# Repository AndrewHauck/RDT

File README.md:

# Missouri S&T Rocket Design
This is the official repository of the Missouri Rocket Design Team. The purpose of this repository is to allow collaboration on PCB development and software development

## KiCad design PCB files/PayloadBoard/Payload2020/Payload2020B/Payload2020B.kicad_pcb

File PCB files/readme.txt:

The home of all RDT board design projects

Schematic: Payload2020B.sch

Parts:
H1, H2, H3, H4: Corner; MountingHole_4-40
J1: BridgeConn; JST_SH_SM15B-SRSS-TB_1x15-1MP_P1.00mm_Horizontal
U1: Xbee_XBP9B; XBEE-1
U2: BerryIMUv3; BerryGPS-IMU_V3

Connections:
+3.3VA: J1.5, U1.1 (VCC)
+3V3: J1.10, U2.1
/Berry_SCL: J1.2, U2.3
/Berry_SDA: J1.1, U2.2
/RX_GPS: J1.3, U2.7
/TX_GPS: J1.4, U2.8
/XBEE_CTS: J1.7, U1.12 (~CTS)
/XBEE_DIN: J1.9, U1.3 (DIN)
/XBEE_DOUT: J1.8, U1.2 (DOUT)
/XBEE_RTS: J1.6, U1.16 (~RTS)
GNDREF: U1.10 (GND), U2.6
unnamed: J1.11, U2.9
unnamed: J1.12, U2.10
unnamed: J1.13, U2.11
unnamed: J1.14, U2.12
unnamed: J1.15, U2.13

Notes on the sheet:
2020 Payload Board B
Project created Feb 16 2020
10mil grid
Xbee Serial pins DOUT DIN CTS RTS

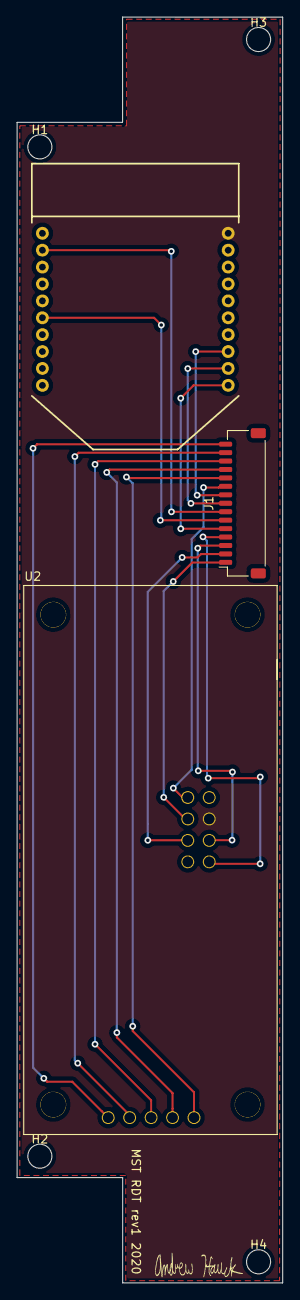
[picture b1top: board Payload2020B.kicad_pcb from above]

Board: 2 copper layers, 31.4 x 149.9 mm, 7 parts (0 on the bottom side), 16 nets.

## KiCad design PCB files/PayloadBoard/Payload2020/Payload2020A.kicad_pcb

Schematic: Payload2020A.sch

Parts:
C1, C2: 1uF; C_1206_3216Metric
C3, C4: 10uF; C_1206_3216Metric
D1, D2: LED; LED_1206_3216Metric
H1, H2, H3, H4: Corner; MountingHole_4-40
J1: BATTERY; JST_XH_B2B-XH-AM_1x02_P2.50mm_Vertical
J2: BridgeConn; JST_SH_SM15B-SRSS-TB_1x15-1MP_P1.00mm_Horizontal
J3: LoadCell; Molex_PicoBlade_53047-0410_1x04_P1.25mm_Vertical
L1: 2.2uH; L_1210_3225Metric
Q1, Q2: Q_NMOS_GSD; SOT-23
R1: 1k; R_0805_2012Metric_Pad1.15x1.40mm_HandSolder
R2: 100k; R_0805_2012Metric_Pad1.15x1.40mm_HandSolder
R3, R6: 100; R_0805_2012Metric_Pad1.15x1.40mm_HandSolder
R4, R5: 10k; R_0805_2012Metric_Pad1.15x1.40mm_HandSolder
SW1: SW_SPST; GW12RCH
U1: Teensy3.6; Teensy35_36
U2: ArduCam
U3: HX711_Breakout
U4: AP7370-50W5-7; SOT-23-5
U5: TPS613222ADBVR; SOT-23-5

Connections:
+3.3VA: C2.1, J2.5, U4.5
+3V3: J2.10, U1.26 (3V3), U2.6 (VCC), U3.10 (VCC)
+5V: C3.1, C4.1, D1.2, D2.2, R1.1, R4.1, U1.53 (VIN), U5.4
/Ardu_CS: U1.11 (9_PWM_RX2_CS0), U2.1 (CS)
/Ardu_MISO: U1.14 (12_MISO0), U2.3 (MISO)
/Ardu_MOSI: U1.13 (11_MOSI0), U2.2 (MOSI)
/Ardu_SCK: U1.40 (13_SCK0_LED), U2.4 (SCK)
/Ardu_SCL: U1.45 (18_A4_SDA0_TOUCH)
/Ardu_SDA: U1.46 (19_A5_SCL0_TOUCH)
/Berry_SCL: J2.2, U1.5 (3_PWM_CAN0TX_SCL2)
/Berry_SDA: J2.1, U1.6 (4_PWM_CAN0RX_SDA2)
/DEN_G: J2.11, U1.7 (5_PWM_TX1_MISO1)
/DRDY_G: J2.13, U1.10 (8_TX3_MISO0_SDA0)
/HX_CLK: U1.3 (1_TX1_MISO1_TOUCH), U3.9 (SCK)
/HX_OUT: U1.2 (0_RX1_MOSI1_TOUCH), U3.8 (DOUT)
/INT1_XM: J2.14, U1.12 (10_PWM_TX2_CS0)
/INT2_XM: J2.15, U1.15 (3.3V)
/INT_G: J2.12, U1.9 (7_RX3_MISO0_SCL0)
/RX_GPS: J2.3, U1.19 (27_RX1)
/TX_GPS: J2.4, U1.18 (26_TX1)
/USR_LED1: Q1.1, R1.2, R2.1, U1.4 (2_PWM)
/USR_LED2: Q2.1, R4.2, R5.1, U1.8 (6_PWM)
/XBEE_CTS: J2.7, U1.17 (25)
/XBEE_DIN: J2.9, U1.21 (29_PWM_CAN0TX_TOUCH)
/XBEE_DOUT: J2.8, U1.20 (28)
/XBEE_RTS: J2.6, U1.16 (24)
GNDREF: C1.1, C2.2, C3.2, C4.2, J1.2, R2.2, R3.2, R5.2, R6.2, U1.1 (GND), U1.27 (GND), U1.39 (GND), U1.52 (AGND), U1.~ (3.3V), U2.5 (GND), U3.7 (GND), U4.2, U5.2
unnamed: C1.2, L1.1, SW1.2, U4.1
unnamed: D1.1, Q1.3
unnamed: D2.1, Q2.3
unnamed: J1.1, SW1.1
unnamed: J3.1, U3.1 (E+)
unnamed: J3.2, U3.2 (E-)
unnamed: J3.3, U3.3 (A-)
unnamed: J3.4, U3.4 (A+)
unnamed: L1.2, U5.1
unnamed: Q1.2, R3.1
unnamed: Q2.2, R6.1
unnamed: U1.34 (37_A18_PWM_SCL1), U2.8 (SCL)
unnamed: U1.35 (38_A19_PWM_SDA1), U2.7 (SDA)

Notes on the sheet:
2020 Payload board A
Project created 2/15/2020
Load Cell ADC
3-4.2V
1sXp LiON
3V3A - Power to Xbee from battery 3V3 - Power to ArduCam, HX711, and BerryIMU from Teensy
<--- from boost converter
Voltage Boost/Regulation
USER CONTROLLED LEDS

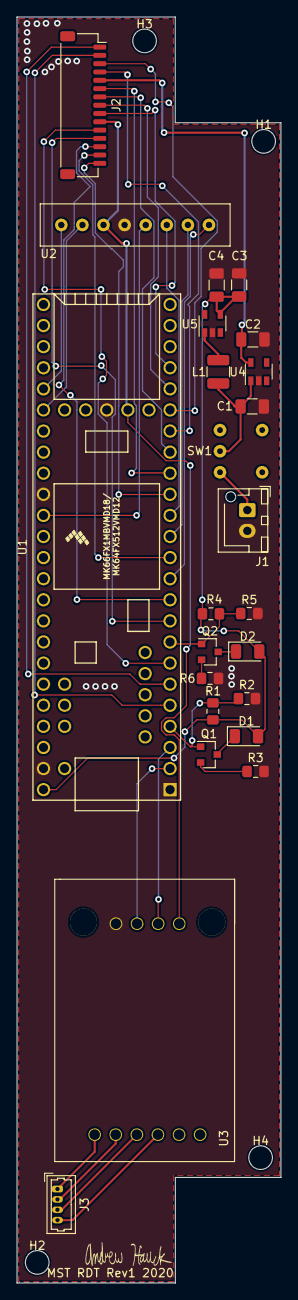
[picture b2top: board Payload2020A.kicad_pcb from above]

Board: 2 copper layers, 31.8 x 152.4 mm, 28 parts (0 on the bottom side), 38 nets.

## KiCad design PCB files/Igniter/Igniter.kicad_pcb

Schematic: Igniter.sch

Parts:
D1: D_Small; D_SOD-123F
D2, D3, D4, D5, D6: D; D_SOD-123F
D7, D8, D9, D10, D11: LED; LED_1206_3216Metric
D12: 3V3; LED_1206_3216Metric
D13: 24V; LED_1206_3216Metric
D14: ACT; LED_1206_3216Metric
F1: BladeFuse; FuseHolder
IC1: 74HC4050; SOP-16_4.4x10.4mm_P1.27mm
J1, J2, J3, J4: PT; Molex_SPOX_5267-03A_1x03_P2.50mm_Vertical
J5: Battery; Molex_Mini-Fit_Jr_5566-02A_2x01_P4.20mm_Vertical
J6, J7: COIL; BananaJack15.5mm
J8, J9, J10, J11, J12: SL1; Molex_SPOX_5267-03A_1x03_P2.50mm_Vertical
J13: Micro_SD_Card; microSD_HC_Hirose_DM3BT-DSF-PEJS
MH1, MH2, MH3, MH4: MountingHole; MountingHole_3.5mm
Q1: IGN; SOT-223
Q2, Q3, Q4, Q5, Q6: Q_NMOS_GDSD; SOT-223
R1: 200; R_1206_3216Metric
R2, R3, R6, R11, R12, R15: 10k; R_1206_3216Metric
R4, R5, R7, R8, R9, R10: 1k2; R_1206_3216Metric
R13: 1k; R_1206_3216Metric
SW1: ARM; R1966ABLKBLKFR-SPST
U1: Teensy3.2; Teensy30_31_32_LC
U2, U3, U4: FDS8984; SO-8_5.3x6.2mm_P1.27mm

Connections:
+3V3: IC1.1 (VCC), J13.4 (VDD), R1.2, U1.15, U1.26, U1.51
+24V: D1.1 (K), D2.1 (K), D3.1 (K), D4.1 (K), D5.1 (K), D6.1 (K), F1.1 (A), F1.2 (A), F1.3 (A), F1.4 (A), J1.3, J2.3, J3.3, J4.3, J6.1, J6.2, J8.3, J9.3, J10.3, J11.3, J12.3, R4.2, U2.5 (Drain2), U2.6 (Drain2), U2.7 (Drain1), U2.8 (Drain1), U3.5 (Drain2), U3.6 (Drain2), U3.7 (Drain1), U3.8 (Drain1), U4.7 (Drain1), U4.8 (Drain1)
/PT0: J1.2, U1.44
/PT1: J2.2, U1.43
/PT2: J3.2, U1.42
/PT3: J4.2, U1.41
/SOL1: Q2.1 (G), R15.1, U1.5, U2.2 (Gate1)
/SOL2: Q3.1 (G), R2.1, U1.6, U2.4 (Gate2)
/SOL3: Q4.1 (G), R3.1, U1.7, U3.2 (Gate1)
/SOL4: Q5.1 (G), R11.1, U1.8, U3.4 (Gate2)
/SOL5: Q6.1 (G), R12.1, U1.9, U4.2 (Gate1)
/SPRK: Q1.1 (G), R6.2, U1.4
GNDREF: D7.1 (K), D8.1 (K), D9.1 (K), D10.1 (K), D11.1 (K), D12.1 (K), D13.1 (K), IC1.8 (GND), IC1.14 (6A), J1.1, J2.1, J3.1, J4.1, J5.2, J8.1, J9.1, J10.1, J11.1, J12.1, J13.6 (VSS), Q1.3 (S), Q2.3 (S), Q3.3 (S), Q4.3 (S), Q5.3 (S), Q6.3 (S), R2.2, R3.2, R6.1, R11.2, R12.2, R15.2, U1.1, U1.27, U1.39, U1.52
unnamed: D1.2 (A), J7.1, J7.2, Q1.2 (D), Q1.4 (D)
unnamed: D2.2 (A), J8.2, Q2.2 (D), Q2.4 (D)
unnamed: D3.2 (A), J9.2, Q3.2 (D), Q3.4 (D)
unnamed: D4.2 (A), J10.2, Q4.2 (D), Q4.4 (D)
unnamed: D5.2 (A), J11.2, Q5.2 (D), Q5.4 (D)
unnamed: D6.2 (A), J12.2, Q6.2 (D), Q6.4 (D)
unnamed: D7.2 (A), R5.1
unnamed: D8.2 (A), R8.2
unnamed: D9.2 (A), R7.1
unnamed: D10.2 (A), R9.2
unnamed: D11.2 (A), R10.2
unnamed: D12.2 (A), R1.1
unnamed: D13.2 (A), R4.1
unnamed: D14.1 (K), R13.2
unnamed: D14.2 (A), IC1.10 (4Y), J13.7 (DAT0)
unnamed: F1.5 (B), F1.6 (B), F1.7 (B), F1.8 (B), SW1.1 (A)
unnamed: IC1.2 (1Y), J13.5 (CLK)
unnamed: IC1.4 (2Y), J13.3 (CMD)
unnamed: IC1.6 (3Y), J13.2 (DAT3/CD), R13.1
unnamed: J5.1, SW1.2 (B)
unnamed: R5.2, U2.3 (Source2)
unnamed: R7.2, U3.3 (Source2)
unnamed: R8.1, U2.1 (Source1)
unnamed: R9.1, U3.1 (Source1)
unnamed: R10.1, U4.1 (Source1)

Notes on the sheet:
24V battery connection
Status Indicators
Board Standoffs
Pressure Transducers
Vcc 200mA max current draw for ATmega2560 -SD card powered by atmega 3V3 pin
-Board sits at test operator area
NOTES
Igniter Arduino Shield
10 mil grid
Solenoid indicators
Igniter Driver
Solenoid Drivers

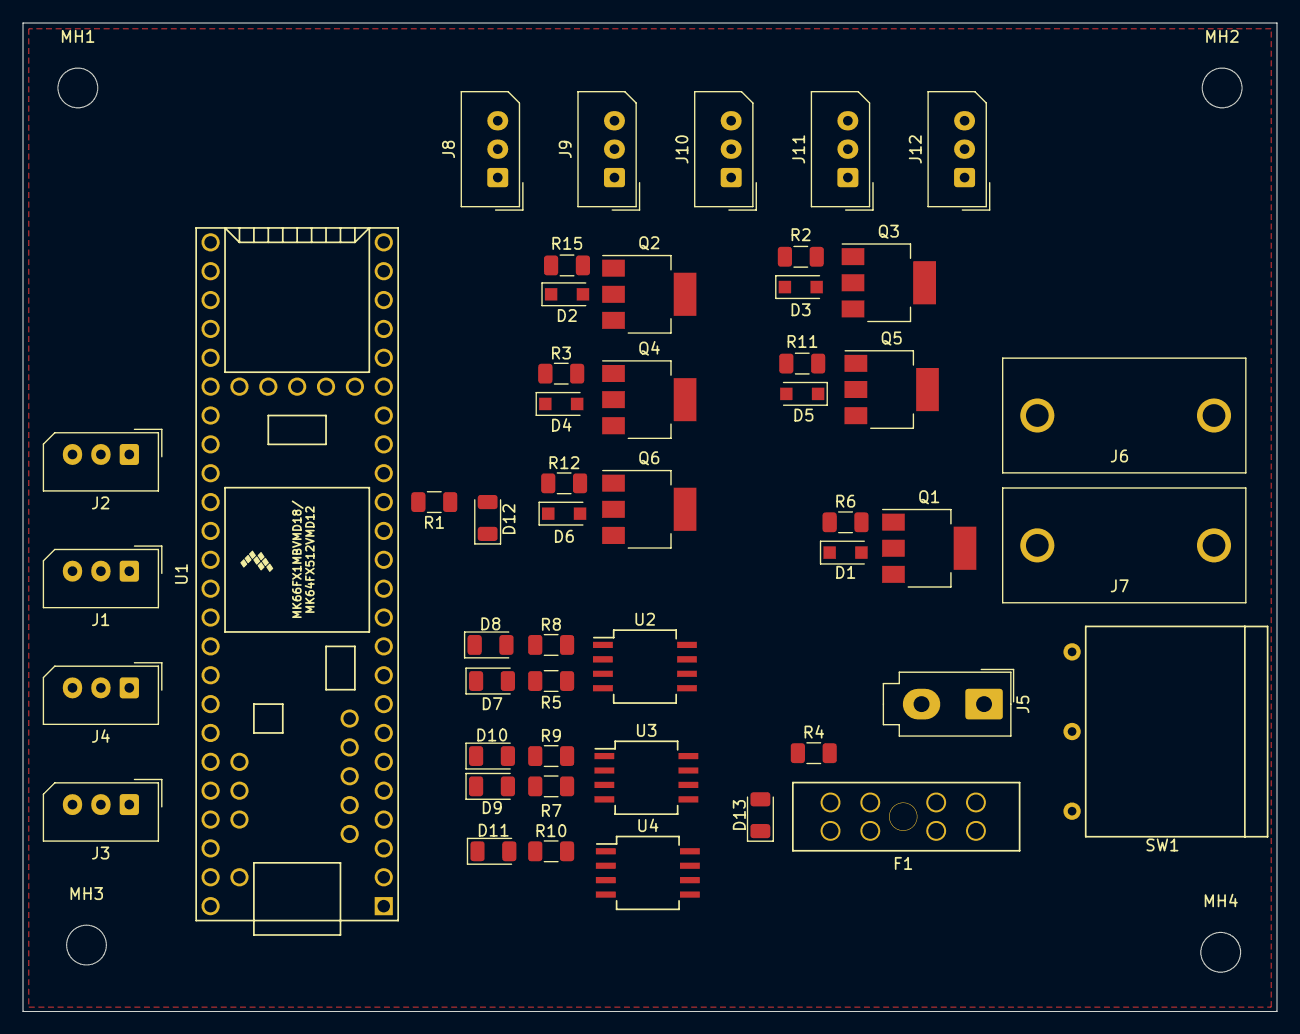
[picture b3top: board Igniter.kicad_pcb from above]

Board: 2 copper layers, 110.4 x 87.0 mm, 54 parts (0 on the bottom side), 33 nets, no tracks yet.

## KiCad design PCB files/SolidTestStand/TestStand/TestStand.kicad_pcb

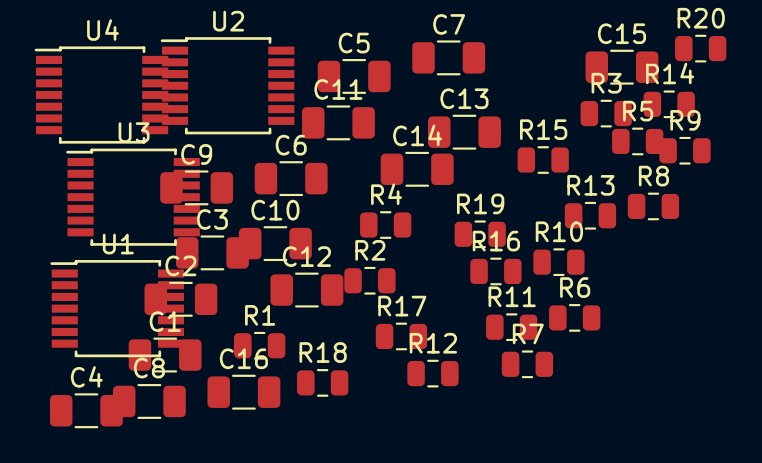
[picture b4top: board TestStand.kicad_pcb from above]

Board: 2 copper layers, 40 parts (0 on the bottom side), 17 nets, no tracks yet.

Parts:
C1, C3, C4, C6, C9, C11, C12, C14: 0.01u; C_1206_3216Metric
C2, C5, C7, C8, C10, C13, C15, C16: 0.1u; C_1206_3216Metric
R1, R2, R3, R4, R11, R12, R13, R14: 100; R_0805_2012Metric
R5, R6, R7, R8, R9, R10, R15, R16, R17, R18, R19, R20: 10k; R_0805_2012Metric
U1, U2, U3, U4: MAX31856; TSSOP-14_4.4x5mm_P0.65mm

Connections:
+3V3: C7.2, C8.2, C15.2, C16.2, R5.2, R6.2, R7.2, R8.2, R9.2, R10.2, R15.2, R16.2, R17.2, R18.2, R19.2, R20.2, U1.5, U1.8, U2.5, U2.8, U3.5, U3.8, U4.5, U4.8
/BIAS: R1.2, R3.2, R11.2, R13.2, U1.2, U2.2, U3.2, U4.2
/SCK: R7.1, R8.1, R17.1, R18.1, U1.10, U2.10, U3.10, U4.10
/SDI: R5.1, R6.1, R15.1, R16.1, U1.12, U2.12, U3.12, U4.12
/SDO: U1.11, U2.11, U3.11, U4.11
/~CS: R9.1, R10.1, R19.1, R20.1, U1.9, U2.9, U3.9, U4.9
/~DRDY: U1.7, U2.7, U3.7, U4.7
/~FAULT: U1.13, U2.13, U3.13, U4.13
GNDREF: C1.1, C3.2, C4.1, C6.2, C7.1, C8.1, C9.1, C11.2, C12.1, C14.2, C15.1, C16.1, U1.1, U1.14, U2.1, U2.14, U3.1, U3.14, U4.1, U4.14
unnamed: C1.2, C2.1, R1.1, U1.3
unnamed: C2.2, C3.1, R2.1, U1.4
unnamed: C4.2, C5.1, R3.1, U2.3
unnamed: C5.2, C6.1, R4.1, U2.4
unnamed: C9.2, C10.1, R11.1, U3.3
unnamed: C10.2, C11.1, R12.1, U3.4
unnamed: C12.2, C13.1, R13.1, U4.3
unnamed: C13.2, C14.1, R14.1, U4.4

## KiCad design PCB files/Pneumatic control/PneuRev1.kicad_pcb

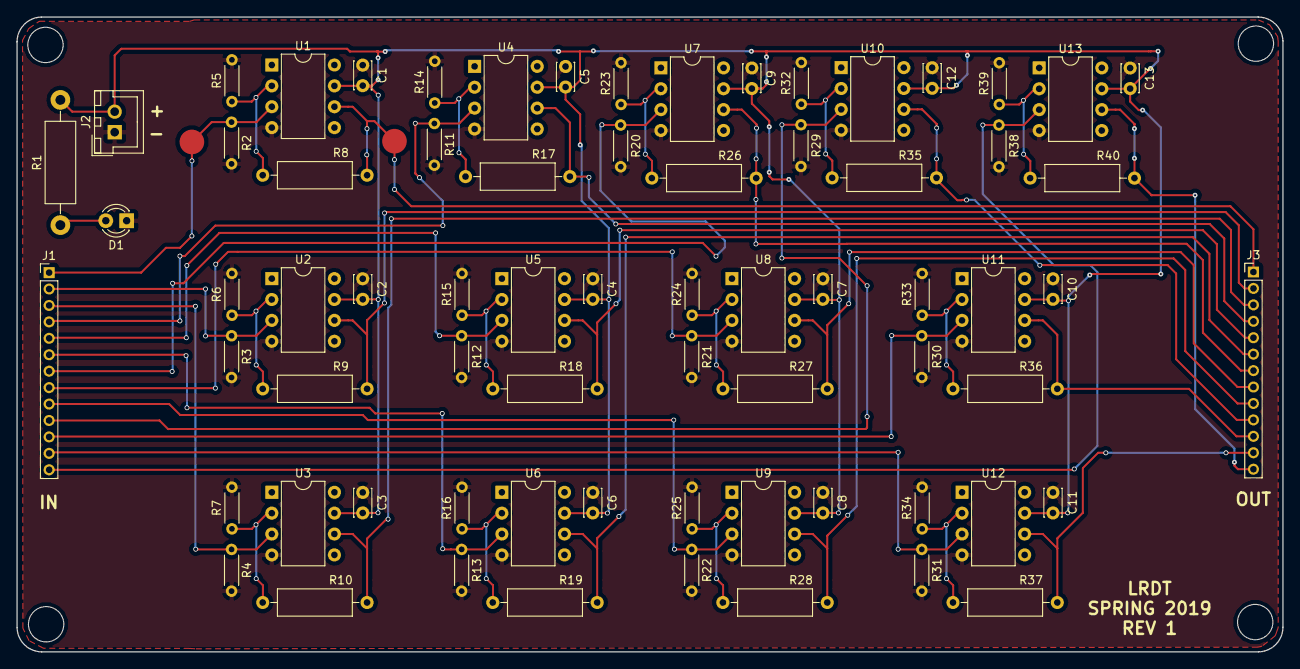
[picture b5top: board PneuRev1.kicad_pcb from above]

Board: 2 copper layers, 154.1 x 77.3 mm, 72 parts (0 on the bottom side), 42 nets.

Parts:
C1, C2, C3, C4, C5, C6, C7, C8, C9, C10, C11, C12, C13: 1uF; C_Disc_D3.4mm_W2.1mm_P2.50mm
D1: LED; LED_D3.0mm
J1: SIG_IN; Pin_Header_Straight_1x13_Pitch2.00mm
J2: BATT_IN; JST_XH_B02B-XH-A_02x2.50mm_Straight
J3: PNEU; Pin_Header_Straight_1x13_Pitch2.00mm
R1: 3k; R_Axial_DIN0411_L9.9mm_D3.6mm_P15.24mm_Horizontal
R2, R3, R4, R5, R6, R7, R11, R12, R13, R14, R15, R16, R20, R21, R22, R23, R24, R25, R29, R30, R31, R32, R33, R34, R38, R39: 1k; R_Axial_DIN0204_L3.6mm_D1.6mm_P5.08mm_Horizontal
R8, R9, R10, R17, R18, R19, R26, R27, R28, R35, R36, R37, R40: 4k; R_Axial_DIN0309_L9.0mm_D3.2mm_P12.70mm_Horizontal
TP1, TP2: TEST; Measurement_Point_Round-SMD-Pad_Big
U1, U2, U3, U4, U5, U6, U7, U8, U9, U10, U11, U12, U13: OPA551; DIP-8_W7.62mm

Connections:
/IN2: J1.2, R3.1, U2.3
/IN3: J1.3, R4.1, U3.3
/IN4: J1.4, R11.1, U4.3
/IN5: J1.5, R12.1, U5.3
/IN6: J1.6, R13.1, U6.3
/IN7: J1.7, R20.1, U7.3
/IN8: J1.8, R21.1, U8.3
/IN9: J1.9, R22.1, U9.3
/IN10: J1.10, R29.1, U10.3
/IN11: J1.11, R30.1, U11.3
/IN12: J1.12, R31.1, U12.3
/IN13: J1.13, R38.1, U13.3
/PNU1: J3.1, R8.2, TP2.1, U1.6
/PNU2: J3.2, R9.2, U2.6
/PNU3: J3.3, R10.2, U3.6
/PNU4: J3.4, R17.2, U4.6
/PNU5: J3.5, R18.2, U5.6
/PNU6: J3.6, R19.2, U6.6
/PNU7: J3.7, R26.2, U7.6
/PNU8: J3.8, R27.2, U8.6
/PNU9: J3.9, R28.2, U9.6
/PNU10: J3.10, R35.2, U10.6
/PNU11: J3.11, R36.2, U11.6
/PNU12: J3.12, R37.2, U12.6
/PNU13: J3.13, R40.2, U13.6
GND: C1.1, C2.1, C3.1, C4.1, C5.1, C6.1, C7.1, C8.1, C9.1, C10.1, C11.1, C12.1, C13.1, D1.1, J2.1, R2.2, R3.2, R4.2, R5.2, R6.2, R7.2, R11.2, R12.2, R13.2, R14.2, R15.2, R16.2, R20.2, R21.2, R22.2, R23.2, R24.2, R25.2, R29.2, R30.2, R31.2, R32.2, R33.2, R34.2, R38.2, R39.2, U1.4, U2.4, U3.4, U4.4, U5.4, U6.4, U7.4, U8.4, U9.4, U10.4, U11.4, U12.4, U13.4
unnamed: C1.2, C2.2, C3.2, C4.2, C5.2, C6.2, C7.2, C8.2, C9.2, C10.2, C11.2, C12.2, C13.2, J2.2, R1.2, U1.7, U2.7, U3.7, U4.7, U5.7, U6.7, U7.7, U8.7, U9.7, U10.7, U11.7, U12.7, U13.7
unnamed: D1.2, R1.1
unnamed: J1.1, R2.1, TP1.1, U1.3
unnamed: R5.1, R8.1, U1.2
unnamed: R6.1, R9.1, U2.2
unnamed: R7.1, R10.1, U3.2
unnamed: R14.1, R17.1, U4.2
unnamed: R15.1, R18.1, U5.2
unnamed: R16.1, R19.1, U6.2
unnamed: R23.1, R26.1, U7.2
unnamed: R24.1, R27.1, U8.2
unnamed: R25.1, R28.1, U9.2
unnamed: R32.1, R35.1, U10.2
unnamed: R33.1, R36.1, U11.2
unnamed: R34.1, R37.1, U12.2
unnamed: R39.1, R40.1, U13.2

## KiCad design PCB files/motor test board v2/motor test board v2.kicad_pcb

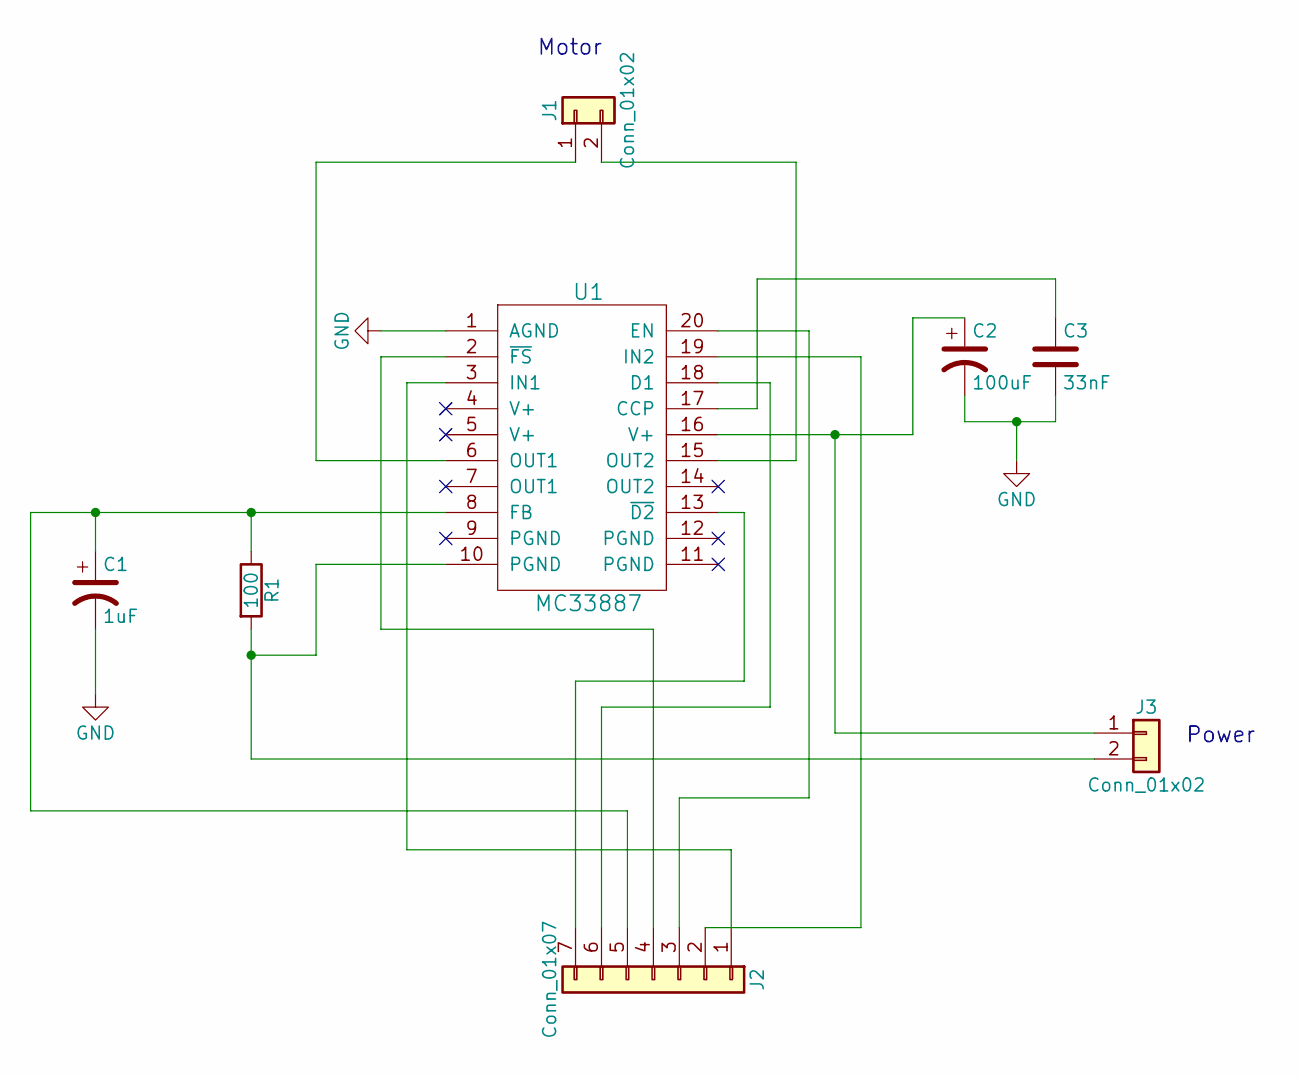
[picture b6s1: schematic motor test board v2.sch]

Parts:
C1: 1uF; CP_Tantalum_Case-C_EIA-6032-28_Hand
C2: 100uF; CP_Elec_8x6.5
C3: 33nF; C_1812_HandSoldering
J1, J3: Conn_01x02; TerminalBlock_Altech_AK300-2_P5.00mm
J2: Conn_01x07; Pin_Header_Straight_1x07_Pitch2.00mm
R1: 100; R_2512_HandSoldering
U1: MC33887; SOIC127P1420X340-21N

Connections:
GND: C1.2, C2.2, C3.2, U1.1 (AGND)
unnamed: C1.1, J2.5, R1.1, U1.8 (FB)
unnamed: C2.1, J3.1, U1.16 (V+)
unnamed: C3.1, U1.17 (CCP)
unnamed: J1.1, U1.6 (OUT1)
unnamed: J1.2, U1.15 (OUT2)
unnamed: J2.1, U1.3 (IN1)
unnamed: J2.2, U1.19 (IN2)
unnamed: J2.3, U1.20 (EN)
unnamed: J2.4, U1.2 (~FS)
unnamed: J2.6, U1.18 (D1)
unnamed: J2.7, U1.13 (~D2)
unnamed: J3.2, R1.2, U1.10 (PGND)

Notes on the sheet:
Motor
Power

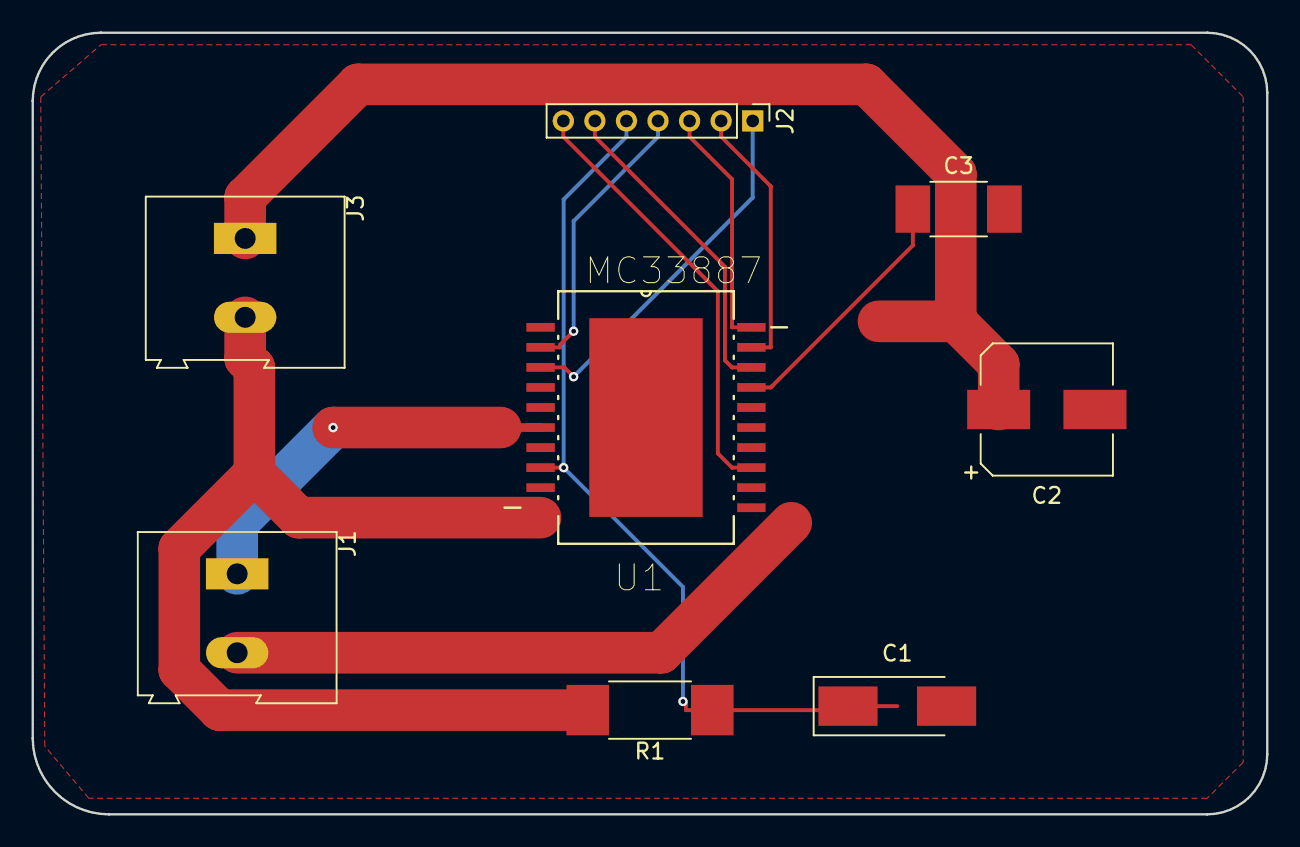
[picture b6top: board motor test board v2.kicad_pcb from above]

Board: 2 copper layers, 78.2 x 49.5 mm, 8 parts (0 on the bottom side), 13 nets.

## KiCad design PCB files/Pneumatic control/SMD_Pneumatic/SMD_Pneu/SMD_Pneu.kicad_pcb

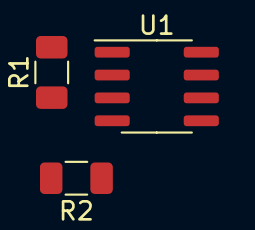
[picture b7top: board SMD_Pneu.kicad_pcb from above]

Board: 2 copper layers, 3 parts (0 on the bottom side), 2 nets, no tracks yet.

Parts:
R1, R2: R; R_1206_3216Metric
U1: LM321; SOIC-8_3.9x4.9mm_P1.27mm

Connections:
unnamed: R1.1, R2.2, U1.3
unnamed: R2.1, U1.4

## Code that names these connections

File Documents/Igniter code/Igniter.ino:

/*
OFFICIAL ROCKET IGNITER CODE
This .ino file is the main program to be run on the 2560 board

 * SD card attached to SPI bus as follows on MEGA2560:
 ** MOSI = DI - pin 51
 ** MISO = DO - pin 50
 ** CLK - pin 52
 ** CS - pin 53

 */
#include <SPI.h>
#include <SD.h>

File myFile;

//Define pressure transducer analog pin variables
int PT1 = A0;
int PT2 = A1;
int PT3 = A2;
int PT4 = A3;

//Define variables for raw data read on analog pins
int pdata1;
int pdata2;
int pdata3;
int pdata4;

//Define pressure pin voltage variables
float V1 = A0;
float V2 = A1;
float V3 = A2;
float V4 = A3;

//Define pressure variables
float P1;
float P2;
float P3;
float P4;

//Time in msec for delay function
int sleep=200;

//Define SPI pins for SD card interface
int CS = 53;
int MOSI = 51;
int MISO = 50;
int CLK = 52;

void setup()
{
  pinMode(3, OUTPUT);
  // Open serial communications and wait for port to open:
  Serial.begin(9600);
  while (!Serial)
  {
    ; // wait for serial port to connect. Needed for native USB port only
  }


  Serial.print("Initializing SD card...");

  if (!SD.begin(CS)) {
    Serial.println("initialization failed!");
    while (1);
  }
  Serial.println("initialization done.");

  if (SD.exists("example.txt")) {
    Serial.println("example.txt exists.");
  } else {
    Serial.println("example.txt doesn't exist.");
  }

  // open a new file and immediately close it:
  Serial.println("Creating example.txt...");
  myFile = SD.open("example.txt", FILE_WRITE);

  if (myFile)
  {
    Serial.print("Writing to SD...");
    myFile.println("Testing");
    myFile.close();
  }
}

void loop()
{
  pdata1 = analogRead(PT1);
  V1 = pdata1*(5.0/1023.0);
  P1 = (14000/2500)*V1;
  //Serial.print("Raw value: ");
  //Serial.print(raw);
  //Serial.print(", Voltage out: ");
  //Serial.println(Vo);
  //Serial.print(", Pressure(psi): ");
  Serial.println(P1);
  delay(sleep);
}

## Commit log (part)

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2018-02-08 removed file
2018-02-08 removed text
2018-02-08 filled GND zone
2018-02-15 Created folder for pcb/docs
2018-02-15 500psiPressureTransducer
    Arduino code to read data from a 500 psi pressure transducer.
2018-02-24 Add files via upload
    Arduino code to test the LRDT igniter.
2018-02-27 2/26/2018
2018-03-25 3/24/18
2018-04-02 Igniter Test Code for the Tiva
    Code to test the LRDT igniter using the Tiva. Requires an external SD card. Uses the buttons on the Tiva as user inputs.
2018-04-05 4/5/2018
2018-04-16 4/16/2018
2018-11-15 Project Creation
2018-12-01 11/30/2018
    -Added bus lines
    -Added net names for in/out
2019-01-20 minor changes
2019-02-01 1/31/2019
    -Gave board edge round corners
    -Routed traces for PWR input part of the board
2019-02-04 2/4/2019
    -Fixed schematic opamp numbering issue
    -Relabelled LED limit resistor to 3k
2019-02-11 2/10/2019
    -Changed LED resistor to 1.5k
    -Set BATT connector to a JST
    -Found 383 ohm resistor to replace 390 ohm
2019-02-15 2/15/2019
    -Created symbol for OPA551
2019-02-15 2/15/2019
    -Updated schematic symbols
2019-02-21 2/21/2019
    -Selected capacitor footprint
    -Generated netlist
    -Began re-routing board
2019-02-26 2/26/2019
2019-08-03 test
2019-08-28 8/28/2019
2019-09-21 9/21/2019 AAH
    -Added indicator LEDS to schematic
2019-10-12 10/11
    Arduino uno footprint
2019-10-19 10/19/2019
    BIG updates
    -Reorganized entire schematic
    -Every functional block has a label now
2019-10-20 10/20/2019
    -Added first revision solenoid drive circuit (needs analysis)
2019-10-25 10/24/2019
    footprints?
2019-10-26 10/26/2019
    Successfully added Mega2560 symbol and footprint library
2019-10-26 Commit from Andrew's laptop to add Arduino serial python testing code to repository
2019-10-28 10/27/2019
    More 2560 pins named/connected
2019-10-30 10/30/2019
    -Changed igniter switch circuit to include indicator
2019-10-31 10/31/2019
    Text edits
2019-11-02 11/1/2019
    -Created bananajack footprint
    -Began arranging components on board
2019-11-02 11/2/2019
    -Added board corner standoffs
    -More footprint changes
2019-11-03 11/3/2019
    Added comment
2019-11-04 11/3/2019
    Placed banana jack footprint in github directory
2019-11-08 11/8/2019
    -Completed SD card circuit in schematic
    -Realized we should regulate 24V to 5V to provide current to stay under the atmega2560 limits
2019-11-09 11/8/2019
    -Added voltage regulator
    -Added 3v3 status led
2019-11-09 11/9/2019
    -Fixed regulator symbol
    -Began adding solenoid valve indicators
2019-11-10 11/10/2019
    -Work on solenoid indicator circuit
2019-11-10 11/10/2019
    -Added AAH signature files
2019-11-11 11/11/2019
    -Fixed regulator circuit
    -Visual changes
2019-11-12 11/11/2019
    Added meeting notes
2019-11-12 11/11/2019
    -Completed addition of new blade fuse schematic symbol
2019-11-13 11/13/2019
    -Added MST and rocket team logos to schematic sheets
2019-11-14 11/14/2019
    -Added a couple more mounting holes to keep board from flexing when plugging in connectors
    -5V regulator likely not needed with new p ducers
2019-11-16 11/16/2019
    -Selected smaller MOSFET SOT223
    -Condensed PCB to a much smaller size
    -Added Solenoid pulldowns
    -Added all momentary switches
    -Shrunk all resistors to 1206
2019-11-16 11/16/2019
    -Changed references to group footprints on the board
2019-11-16 11/16/2019
    Opened Igniter documents
2019-11-17 11/17/19
    First test piece of Igniter UI code. Mostly a proof of concept. Does not integrate serial communication
2019-11-24 11/24/2019
    -Moved igniter.ino into its own folder to play nice with arduino
    -Changed sd card variable names to avoid conflicts with header files
2019-11-25 11/24/2019
    -Increased igniter.ino SD timeout length slightly
    -Testing commits with python code changes
2019-11-25 11/25/2019
    -Added all four pressure data calculations
    -Arduino outputs each full sensor read in one string
2019-11-26 11/26/2019
    -Igniter UI now outputs pressure data to corresponding text fields on the UI
    -Each reading updates about every 3 seconds
2019-11-29 11/29/2019
    -Added to igniter.ino to attempt to execute commands given by the UI
    -Added feature to IgniterUI.py that sends a command over serial when the ARM button is clicked
2019-12-01 12/1/2019
    -Set design rules for higher current traces
    -Shrunk board slightly
2019-12-02 Removed space between igniter and UI
2019-12-03 12/2/2019
    -Unofficially changed UI name to RocketView
2019-12-03 12/2/2019
    -Began adding arduino serial interrupts
    -Arduino setup to parse python commands as an interrupt
    -Fixed range from 5 to 6 in IgniterUI.py
2019-12-03 12/2/2019
    -Removed some unncessary, commented out code
    -Playing with using endsWith function for parsing
    -Parsing method for receiving commands still needs to be figured out
2019-12-03 12/3/2019
    PCB
    -edited board outline to be smaller
    -Relocating sensor and solenoid connections to one side of the board
2019-12-05 12/4/2019
    Changed P transducers connector to dsub
    Moved SD card circuit onto main shematic sheet
    😂
2019-12-05 Improved Serial for IgniterUI
    More to follow, plan is to incorporate serial "handshake" between UI and Arduino, make all serial communication functions into own library/file, and eventually incorporate UI elements to select COM p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
2019-12-05 12/5/2019
    -Updated netlist and board layout with added dsub15 for solenoids
    -Fixed all barrel jack connectors
    -Removed some 2560 pins for routing
2019-12-06 Removed Virtual Environment Stuffs
2019-12-09 12/9/2019
    -Picked SPOX vertical molex for pressure transducer connnector
2019-12-18 12/17/2019
    -Board layout changes to make better routing paths, no traces drawn yet
2019-12-21 12/21/2019
    -Added note to resize board corner mounting holes
2020-01-05 Implemented serialPacket and serialBuffer classes
    These two classes handle all the scary formatting necessary for receiving packets to the arduino, as well as transmitting. Next step is to define commands that can be executed when packet of "command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
2020-01-07 Functional packet-based serial communication between IgniterUI and Arduino
    Status: In current build, backend for arduino (classes, header files, etc.) is operational. Reactions to commands need adding, but framework is there.
    Added: Arduino can respond to different packet types ('C' for command, 'M' for message, 'D' for data, etc.). For promo/display purposes, BuiltIn LED responds to stage presses on IgniterUI.
    Changed: IgniterUI used to print out current status, such as "Armed." These has been replaced by "arming..." followed by the message "IGNITER ARMED" being sent from the microcontroller. This is to he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
2020-01-09 1/9/2020
    -Added C&K switch footprint to board
2020-01-11 Early Improved UI Elements and Data Logging
    Arduino:
    Each valve is assigned a digital output pin. Pin states are stored and modified by commands sent from UI Stages buttons
    Stage Buttons:
    Pressing the different stage buttons commands the arduino to configure valve pins to preset states.
    Valve Buttons:
    Valve buttons now are colored based on response from arduino query. Pressing valve buttons command explicit valve to toggle on arduino.
2020-01-12 Added File Logging
    At the bottom of the UI, there are controls to log the pressure values as they are displayed to a file.
    Log Folder Browser:
    The default directory for storing log files is the "Pressure Logs" folder inside the main "Ground Station" directory. Clicking the Browse button allows you to change this.
    Log Files:
    When recording is enabled, a new log file is created with the naming convention IgniterUILog-YYYYMMDD-HHMMSS.txt. The log files record all events along with a timestamp.
2020-01-15 1/15/2020
    Continued board routing work
    -Swapped rocker switch terminals
    -Grouped all board LEDs
    -Changed PCB grid size to 10 mil
2020-01-16 1/16/2020
    -Continued board routing
    -Rearranged board LEDs and added labels
    -Removed hierarchical sheet, combined schematic into one sheet
2020-01-16 Thermocouple board file created
    -Deleted TEST folder
    -Created "TestStandThermo" folder
    -Schematic started
2020-01-17 Finished thermo schematic
    -Taken from adafruit, removed regulator and level shifters
    -Created BOM from KiCAD, exported to google drive (Electronics>Solid>BOM)
2020-01-18 schematic cleanup
2020-01-20 1/20/2020
    -Fixed ground connections being seperated
2020-01-21 Added Teensy kicad symbols & footprints
2020-01-22 Added SD card activity LED to schematic
    -fixed some local net label appearances on schematic
    -Added circuit and selected footprints for the LED and resistor
2020-01-23 Verified fuse holder footprint dimensions
2020-01-24 SolidTestStand project name change
    -deleted Thermo.csv
2020-01-24 Created Thermocouples folder for Jack's code
2020-01-25 1/25/2020
    -Added via stitching for MOSFET circuits
    -U2,3,4 are upside down, added pin 1 dot for assembly purposes
2020-01-27 Updating Arduino-Code branch to final build of my fork
    Learned how Git works, gonna delete my fork and need to pass current work over to Arduino-Code branch
2020-01-27 Added signature to board
    -fixed orientation of dual channel mosfet on board
2020-01-28 Added .gitignore and a requirements.txt Removed system files and __pycache__ from version control
2020-01-28 Updated logging logic and usage, improved program flow
2020-01-29 Condensed code in ArduinoWConfigureWindow
2020-01-29 Fixed bugs to make igniter UI work correctly Moved images to img folder
2020-01-31 Small edits for manufacturing
    -SIlkscreen adjustments
    -fixed switch drill hole diameters
2020-01-31 Final silkscreen edits
2020-02-02 Read netlist
2020-02-05 Added basic files for the solid rocket test fire code.
2020-02-07 Valve states are now represented on igniter diagram, early implementation
    Still to come: removing valve buttons and instead clicking on valves on the diagram.
2020-02-08 2/8/2020
2020-02-08 2/8/2020
    Schematic edits
2020-02-13 Changed MCU to teensy 3.6
    Schematic
    -removed sd card circuit, replaced by teensy onboard sd card holder
    -connected all remaining local nets to teensy
    Board
    -Started basic board layout, grouping of related components
2020-02-13 Removed old, unwanted files
    removed old hierarchical sheets and unintened sd.pro (where did this even come from?)
2020-02-15 test commit
2020-02-15 changed name of Documents folder to Programming, place only code in here
2020-02-15 readme created
    Info on what this folder is for
2020-02-15 Added in progress code for BerryIMU and HX711 load cell ADC chip
2020-02-16 Created Board A symbols
2020-02-19 Added updated test fire instrumentation Pi code (untested)
2020-02-21 Payload board updates 2/20/20
2020-02-22 Board schematic update
    -Created SCL0 and SDA0 local net
2020-02-24 Testing potential library fix -added sym-lib-table to git ignore to prevent overwriting local Kicad library paths when pushing changes -created a test symbol in payload library to verify
2020-02-24 -Created symbol for HX711 chip to allow integrating circuit directly into the payload board
2020-02-24 -Added connector to Board B -Added descriptive i2c local net names
2020-02-25 Payload Board B changes -Added xbee and berry GPS signal pin local nets -Added power and gnd flags to berry and xbee
2020-02-28 Removed 5V regulator Stepped input voltage down to that of a 1s battery pack Added internal parallite battery connection
2020-03-03 Added files to post-process solid test fire data
2020-03-04 -began footprint for berryIMU -Added XBEE sparkfun footprints from github -Added xbee and gps net connection to connector on board A
2020-03-04 Updated boost converter L and C values according to datasheet
2020-03-05 Arranged more components on board -Drew board edges for board B -Added User controlled LEDs
2020-03-06 Changed board sizes based on payload bay dimensions Changed battery connector to JST XH
2020-03-09 Minor visual changes to boards
2020-03-09 Updated postprocessing code to output to a desired file Updated instrument box to wait for lock before trying to close serial port.
2020-03-12 Created 4-40 thread mounting hole Selected 4-40 hole size for Board A
2020-03-17 Created MountingHole 4-40 size footprint
2020-03-20 Checked and fixed alignment of HX711 footprint dimensions Added hx711 mounting hole directly to footprint Redrawn edge cuts to fit into payload bay with about 0.01" fudge factor
2020-03-23 Made a serialHelper library which contains file loading from testFireInstrumentBox
2020-03-23 Added in sample files from test fire
